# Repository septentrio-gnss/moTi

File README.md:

# moTi
| Role        | Contact                                                                 |
|-------------|-------------------------------------------------------------------------|
| Author      | [laekaz](https://github.com/laekaz)                 |
| Maintainer  | [Septentrio GNSS GitHub User](githubuser@septentrio.com)                |
| License     | [OCP CLA](https://www.opencompute.org/documents/ocp-cla)                |
| Project     | [Stargate](https://stargate-receiver.com/)    |

This project is co-funded by the European Union Agency for the Space Programme under the Fundamental Elements Grant EUSPA/GRANT/02/2024

## Table of Contents
* [Introduction](#introduction)
* [What is a moTi?](#what-is-the-moTi)
  * [Can I buy it?](#can-i-buy-it)
* [What is a Time Card?](#what-is-a-time-card)
* [What is a Mosaic-G5 T?](#what-is-a-mosaic-g5-t)
* [Who is Septentrio?](#who-is-septentrio)
  * [Why open-source?](#why-open-source)
* [Disclaimer](#disclaimer)
* [Deliverables](#deliverables)
  * [M.2 Form Factor](#m2-form-factor)
* [User Documentation](#user-documentation)
  * [System Setup](#system-setup)
    * [Boot Linux](#boot-linux)
    * [Check the GNSS Status (Satellite Time)](#check-the-gnss-status-satellite-time)
    * [Output the PPS and Clock](#output-the-pps-and-clock)
    * [Use the PHC from Linux](#use-the-phc-from-linux)
    * [When the Card is Installed and Running](#when-the-card-is-installed-and-running)
    * [If Something Goes Wrong](#if-something-goes-wrong)
* [Design Documentation](#design-documentation)
  * [Ordering Mosaic](#ordering-mosaic)
  * [Board Connections and Indicators](#board-connections-and-indicators)
    * [Pinout for M.2 Key B Connector](#pinout-for-m2-key-b-connector)
    * [USB 2.0](#usb-20)
    * [UART](#uart)
    * [PPS Out](#pps-out)
    * [Event 1 (PPS IN)](#event-1-pps-in)
    * [LED D1](#led-d1)
    * [Antenna Connector](#antenna-connector)
## Introduction 
## What is a moTi?

moTi is a timing module that provides accurate and reliable synchronisation signals for time-sensitive systems. It is based on a standardised M.2 form factor that can be easily integrated into compatible carrier boards such as the Open Compute Project (OCP) [Time Card](#what-is-a-Time-Card?).
This board receives precise timing information from Septentrio’s mosaic-G5 T GNSS (Global Navigation Satellite System) module. It then generates synchronisation outputs such as Pulse Per Second (PPS) and Time of Day (ToD) data. These signals are then used to synchronise services, in network interface cards (NICs), and other hardware in data centres and communication systems.

## What is a Time Card?

A Time Card is a PCIe card that is designed to plug into a server and provides precision time outputs such as PPS (Pulse Per Second) and ToD (Time of Day). It provides this precise timing to the server’s clock and network hardware, enabling high-accuracy synchronisation using protocols like the NTP or PTP. moTi connects to the Time Card as a timing source, supplying the card with GNSS time signals in standardised form factor.

Originally, it was developed by Meta and released through the Open Compute Project

More information about the Time Card on this [link](https://fr.scribd.com/document/803083407/M-2-Sync-Module-OCP-Base-Specification-1-1-1) or [Github](https://github.com/Time-Appliances-Project/Time-Card?tab=readme-ov-file) 

## What is a mosaic-G5 T?
[Septentrio mosaic-G5 T](https://www.septentrio.com/en/products/gnss-receivers/gnss-receiver-modules/mosaic-g5-t) is a compact, low-power GNSS timing receiver module with multi-band, multi-frequency capability. Designed for critical infrastructure and other applications where resilient and precise timing is essential, it ensures maximum security and uptime. It tracks all Global Navigation Satellite System (GNSS) constellations and supports both current and future signals. 

## Who is Septentrio?

Septentrio is a leading company that designs, manufactures and sells high precision and multi-frequency GPS/GNSS receivers for demanding applications. Septentrio products are used in different industries including automotive, marine, construction, rail, machine control, logistics, precision agriculture, geographic information systems (GIS), Unmanned Aerial Vehicles (UAVs), surveying, mapping and scientific development. Septentrio’s receivers constantly deliver accurate and precise GNSS positioning scalable to centimetre-level and designed to perform perfectly in challenging environments. 

Septentrio's technology offers high accuracy and reliability thanks to GNSS + algorithms as well as [Advanced interference Monitoring and Mitigation (AIM+)](https://www.septentrio.com/en/learn-more/advanced-positioning-technology/aim-anti-jamming-protection) This protects your application against jamming (RF interference) and spoofing (malicious attacks).

For more information about Septentrio products go to [**https://www.septentrio.com/**](https://web.septentrio.com/GH-SSN-home).

### Why open-source?
This board is open source to encourage collaboration, customization, and innovation. By making the design files publicly available, developers and engineers can study, modify, and adapt the hardware to fit their specific applications, reducing development time and cost. It also promotes transparency and avoids vendor lock-in, allowing users to fully understand and control the design.

## Disclaimer
This project is offered as-is. The main interfaces have been tested, but the design has not been fully checked or approved by the author or Septentrio. You are responsible for how you use it in your own projects. For guidance on working with Septentrio’s GNSS mosaic modules, we suggest reaching out to Septentrio directly.

Support website: https://www.septentrio.com/en/support

### Deliverables
This open-source project contains the following files for designers, producers and integrators around Septentrio's mosaic modules.
|Files         |description   |
|--------------|--------------|
|[moTi.kicad_pro](./KiCad_Files/KiCad/moTi/moTi.kicad_pro)| KiCAD project|
|[moTi.kicad_sch](./KiCad_Files/KiCad/moTi/moTi.kicad_sch)|KiCAD schematic|
|[mosaic-G5.kicad_sch](./KiCad_Files/KiCad/moTi/mosaic-G5.kicad_sch)|KiCAD mosaic-G5 schematic sheet |
|[M2_Edge connector.kicad_sch](./KiCad_Files/KiCad/moTi/M2_Edge%20connector.kicad_sch)|KiCAD M.2 Key B schematic sheet|
|[Clockdetect.kicad_sch](./KiCad_Files/KiCad/moTi/Clockdetect.kicad_sch)|KiCAD clock schematic sheet|
|[moTi.kicad_pcb](./KiCad_Files/KiCad/moTi/moTi.kicad_pcb)|KiCAD PCB layout|
|[moTi_Schematics.pdf](moTi_Schematics.pdf)|schematic PDF|

#### M.2 form factor

The M.2 form factor provides a compact interface for expansion cards.The moTi board is M.2 Key B connector, but it can also fit into some Key M or B+M slots. B+M slots are designed with extra notches so they accept both Key B and Key M modules, allowing flexibility in installation. This means your Key B board can interconnect with a Key M-compatible slot as long as it’s a B+M slot, ensuring proper electrical connections and compatibility.

## User documentation

### System Setup

Before you physically install anything: 
* Make sure you have a free PCIe slot
* Make sure your BIOS supports Virtualization/IOMMU for Linux use
* You must connect the GNSS antenna to its SMA connector before inserting the Time Card.
##### Boot Linux 
Boot Linux with the Time Card inserted. 

If your Linux system uses the Kernel 5.15 or newer the Time Card driver is already included. So the kernel loads the driver automatically.

The devices are exposed by the driver like:

`/dev/ptpX` -> PHC device 

`/dev/ppsY` -> PPS pulse signal

`/sys/class/timecard/ocp0/`-> status and attributes

These are the time interface paths in the OS.

Command example to see the devices:
```
ls -l /sys/class/timecard/ocp0/
```

This will show many devices including GNSS, PPS, PHC clock and atomic clock serial
##### Check the GNSS status (satellite time)
Once Linux has detected the Time Card:

* GNSS time is usually on a serial port like `/dev/ttyS7` or similar.
* You can run `gpsd` or a tool like `cgps` to check the satellite status.

For example:

```
gpsd /dev/ttyS5
```

* To make sure GPS is sending messages, use tio

```
tio -b 115200 /dev/ttyS5
```
* Check if the FPGA time is correct by checking the NMEA

```
tio -b 115200 /dev/ttyS0
```

##### Output the PPS and Clock
available_sma_outputs contains all available outputs

To list available outputs:
```
cat available_sma_outputs
    10MHz PHC MAC GNSS1 GNSS2 IRIG DCF GEN1 GEN2 GEN3 GEN4 GND VCC
```
```
 cat /sys/class/timecard/ocp0/available_sma_outputs 
```
Output on SMA:
* FPGA PPS 
```
echo OUT: PHC >> sma1
```
* Atomic Clock PPS
```
echo OUT: MAC >> sma1
 ```
* GPS Module's PPS 
```
echo OUT: GNSS1 >> sma1
```

##### Use the PHC from Linux
The PHC (Precision Hardware Clock) device exposed by the driver can be used to sync the Linux system clock

##### When the card is installed and running
Once everything is configured:
* The Time Card provides accurate time to Linux
* You can serve time to network clients using NTP or PTP
* Your system becomes a Stratum 1 time source 

This means your server can act as a time source for the whole infrastructure.

##### If something goes wrong
* If the driver fails to load: make sure you have a newer Linux kernel
* If /dev/ptp doesn’t show: check BIOS PCIe settings
* If no GNSS: verify if antenna is connected.

These are normal steps to get the Time Card recognized by Linux.

## Design documentation
#### Ordering mosaic
For orders of the mosaic-G5 T, please contact [Septentrio](https://www.septentrio.com/en/products/gnss-receivers/gnss-receiver-modules/mosaic-g5-t)

### Block diagram

The above block diagram is showing the overview communication between the antenna, receiver and M.2 edge connector. 

### Board connections and indicators

| interface signals |I/O Type | Voltage | Signal Description |
|-------------------|---------|---------|--------------------|
| Power             | Power   |  3.3V   |3.3 V Supply pin.   |
| UART              |   I&O   |    3.3V | Universal Asynchronous Receiver Transmitter, RX & TX|
|USB                |   I/O   |  3.3V   | Universal Serial Bus interface, USB D+ and D− differential data lines|
| PPS Out 1         |   O     | 3.3V    |Pulse Per Second signal out#1.
| PPS Out 2         |   O     | 3.3V    |Pulse Per Second signal out#2.
| Event 1 (PPS IN)  |   I     |   3.3V  |Pulse Per Second reference signal input. If not used, connect to ground on Platforms.|
| CLK_IN            |   I     | 3.3V    |10MHz reference clock input. If not used, connect to ground|
| CLK_OUT           |   O     | 3.3V    |10MHz output clock.   |
| LED D1            |   O     | 3.3V    |Power Supply indicator|

#### Pinout for M.2 Key B Connector

| Pin # |Signal            |
|-------|------------------|
| 7	    |USB D+            |
| 9	    |USB D-            |
| 23	|10MHz clock input |
| 67	|nRST_IN           |
| 2, 4	|VBAT              |
| 10	|LED#1             |
| 20	|PPS2 output       |
| 22	|Ref_CLK_SEL       |
| 24	|PPS input         |
| 46	|PPS1 output       |
| 48	|10MHz clock output|
| 62	|UART COM1 Rx      |
| 64	|UART COM1 Tx      |
| 70, 72, 74|   Power 3.3V |
| GND	|GND               |

**USB 2.0** pins USB_D+ and USB_D- 
When the module is inserted into a card that supports USB pins on its edge connector, the USB interface works just like it would on any other device. It is used for data, configuration, and control. It carries data such as , Time of Day (ToD) for the GNSS, diagnostic messages and firmware update channels. The Time Card will act as the USB host.

**UART** (Universal Asynchronous Receiver Transmitter)
This is a standard serial port using TX and RX pins.

**PPS Out** timing reference signal output. This supplies high-precision timing references directly into the Time Card clocking system. 

**Event 1 (PPS IN)** This pin detects a pulse from an external device and records the exact GNSS time when the pulse happened. It is connected to the eventB pin of the mosaic-G5 T

##### LED D1

This LED indicates whether the Module is ON/OFF

##### Antenna connector

The board provides a U.FL (UMCC) 50 Ω PCB receptacle for connecting an external GNSS antenna.
This miniature RF connector is commonly used in compact embedded and wireless systems due to its small size and reliable high-frequency performance.

**Connector Details**
* Type: U.FL (UMCC) Receptacle
* Impedance: 50 Ω
* Application: External active/passive GNSS antenna connection

**Notes**
* Use a compatible U.FL/IPX coaxial cable assembly when connecting an antenna.
* Keep RF cable lengths as short as possible to minimize signal loss.
* Ensure the antenna system is properly matched to 50 Ω impedance for optimal RF performance.

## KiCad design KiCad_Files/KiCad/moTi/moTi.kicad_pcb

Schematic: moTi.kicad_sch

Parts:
PCB1: PCB_label

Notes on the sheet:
Project: moTi Varient: mosaic-G5 T
CHANGE LOG
mosaic-G5 T
Ultra-compact high-precision GNSS time synchronization receiver
Table of content
M.2 Key B with Mosaic G5 GNSS Module
Schematics arranged by Laetitia.K

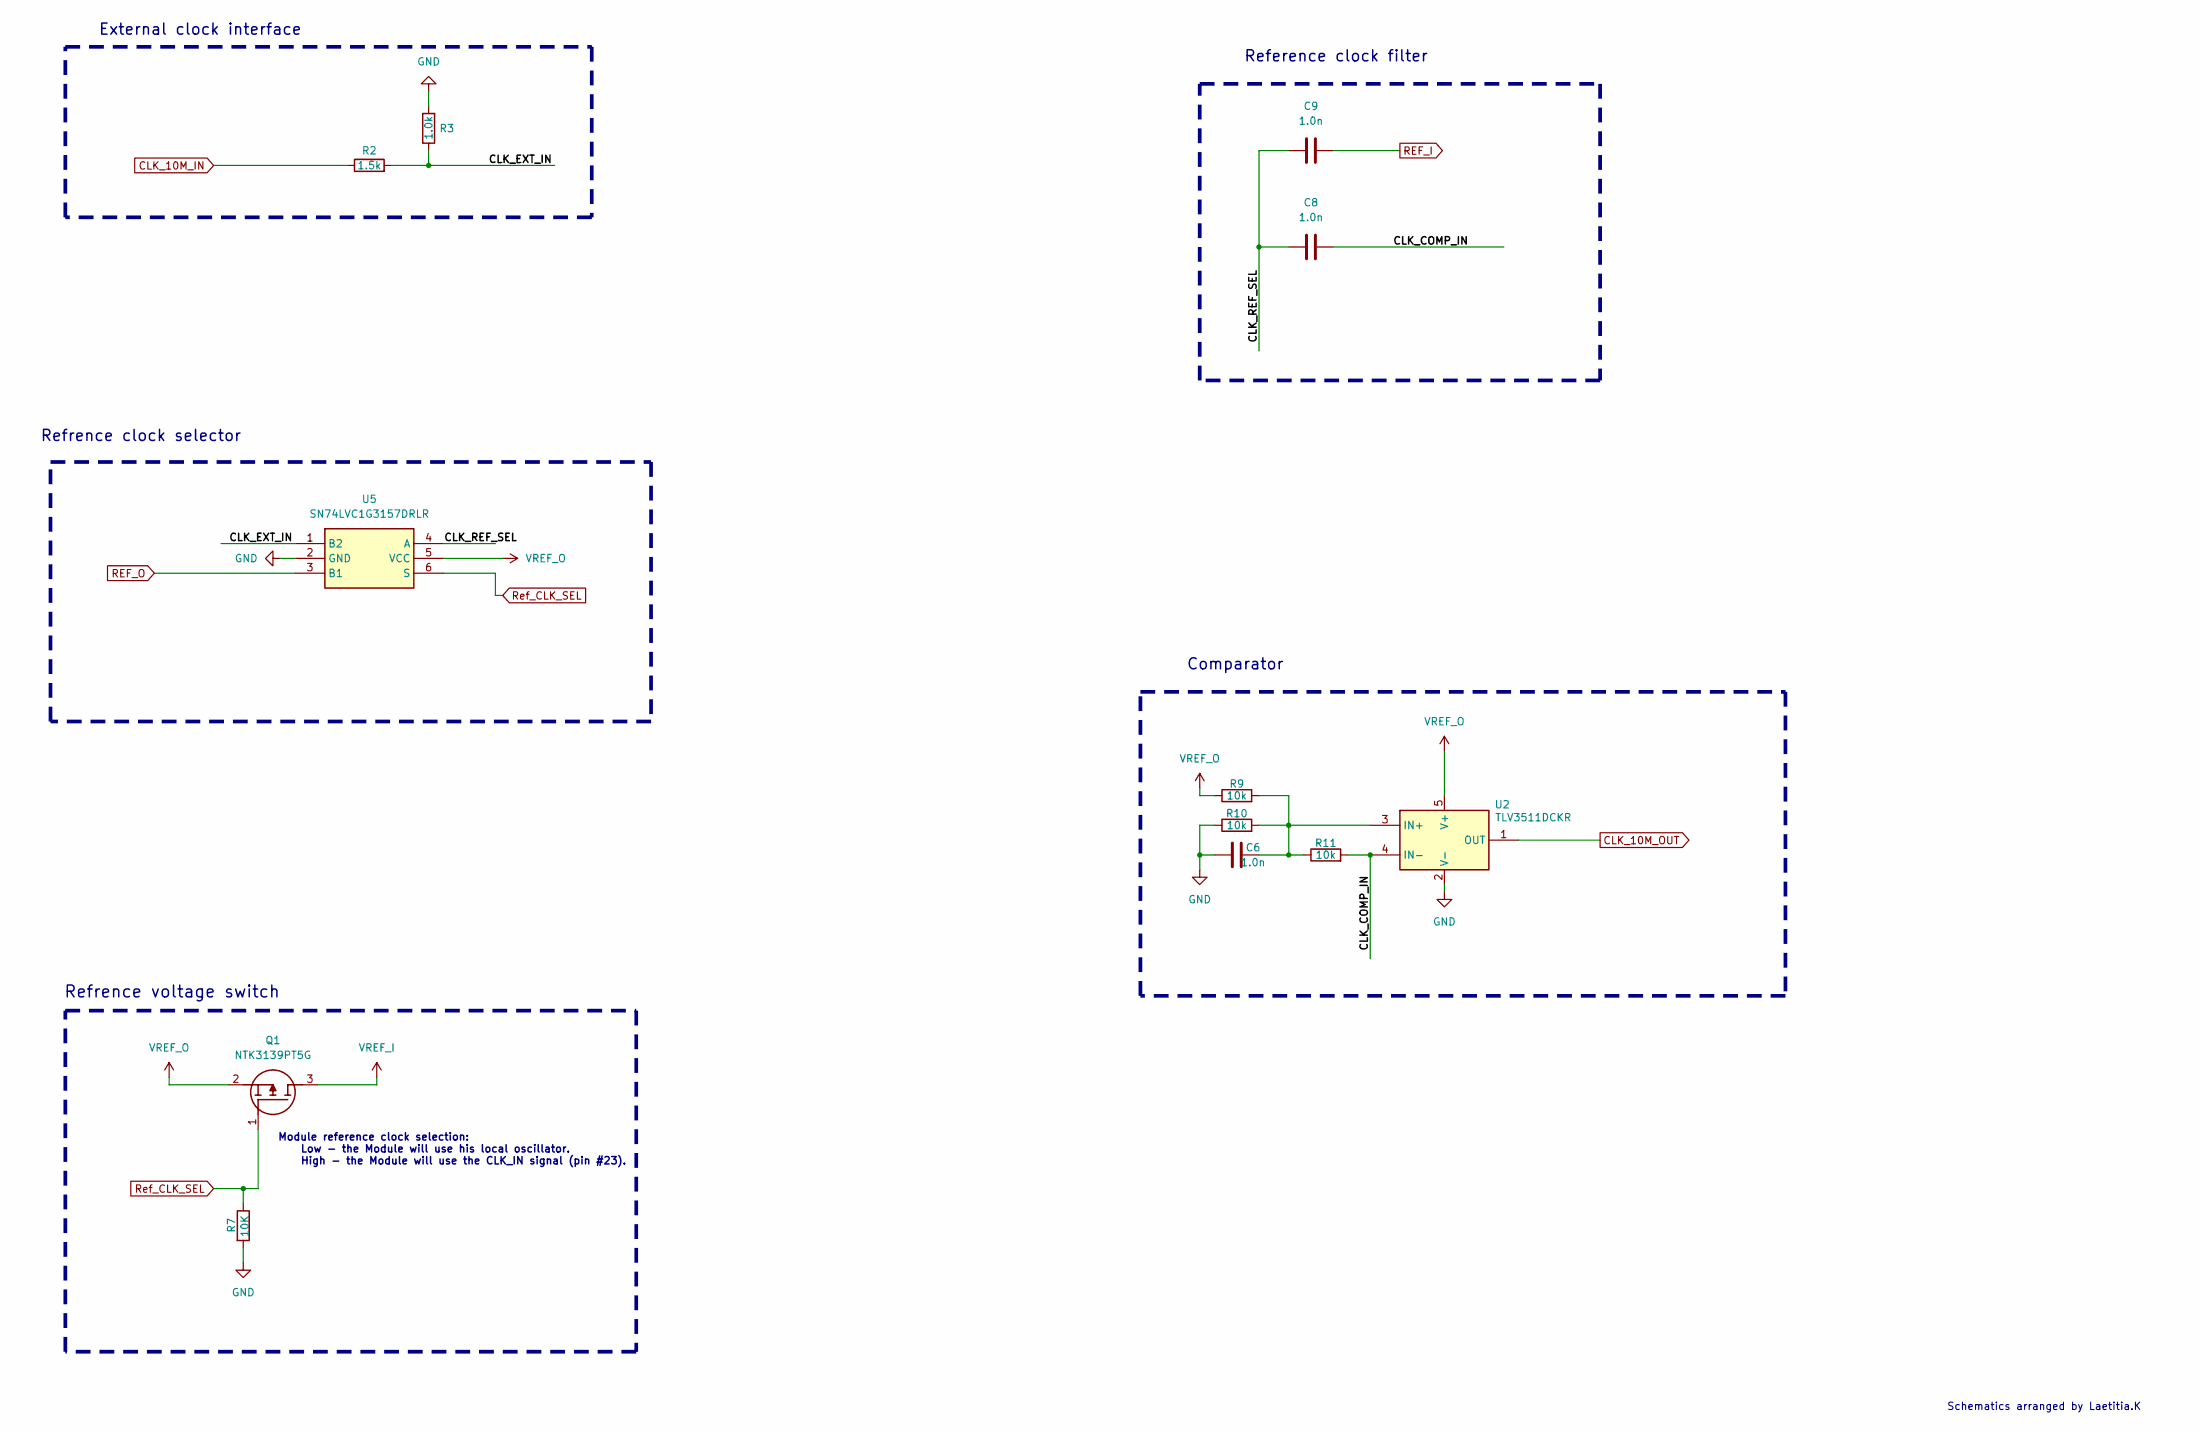
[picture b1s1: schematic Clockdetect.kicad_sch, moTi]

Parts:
C6, C8, C9: 1.0n; C_0402_1005Metric; Manufacturer_Part_Number CC0402KRX7R9BB102
Q1: NTK3139PT5G; SOTFL40P120X55-3N; Manufacturer_Part_Number NTK3139PT5G; Mouser Part Number 863-NTK3139PT5G
R2: 1.5k; R_0402_1005Metric; Manufacturer_Part_Number CRCW04022K20FKED
R3: 1.0k; R_0402_1005Metric; Manufacturer_Part_Number CRCW04021K00FKEDC
R7: 10K
R9, R10, R11: 10k; R_0402_1005Metric; Manufacturer_Part_Number CRCW040210K0FKED
U2: TLV3511DCKR; SOT65P210X110-5N; Manufacturer_Part_Number TLV3511DCKR
U5: SN74LVC1G3157DRLR; SOTFL50P160X60-6N; Mouser Part Number 595-SN74LVC1G3157DRL

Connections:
CLK_10M_IN: R2.1; also elsewhere on the board
CLK_10M_OUT: U2.1 (OUT); also elsewhere on the board
unnamed: C6.2, R9.2, R10.2, R11.1, U2.3 (IN+)
unnamed: C8.2, R11.2, U2.4 (IN-)
unnamed: C8.1, C9.1, U5.4 (A)
unnamed: R2.2, R3.1, U5.1 (B2)
REF_I: C9.2; also elsewhere on the board
REF_O: U5.3 (B1); also elsewhere on the board
VREF_I: Q1.3 (D); also elsewhere on the board
VREF_O: Q1.2 (S), R9.1, U2.5 (V+), U5.5 (VCC); also elsewhere on the board

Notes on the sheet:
Comparator
External clock interface
Reference clock filter
Refrence clock selector
Refrence voltage switch
Module reference clock selection: Low - the Module will use his local oscillator. High - the Module will use the CLK_IN signal (pin #23).
Schematics arranged by Laetitia.K

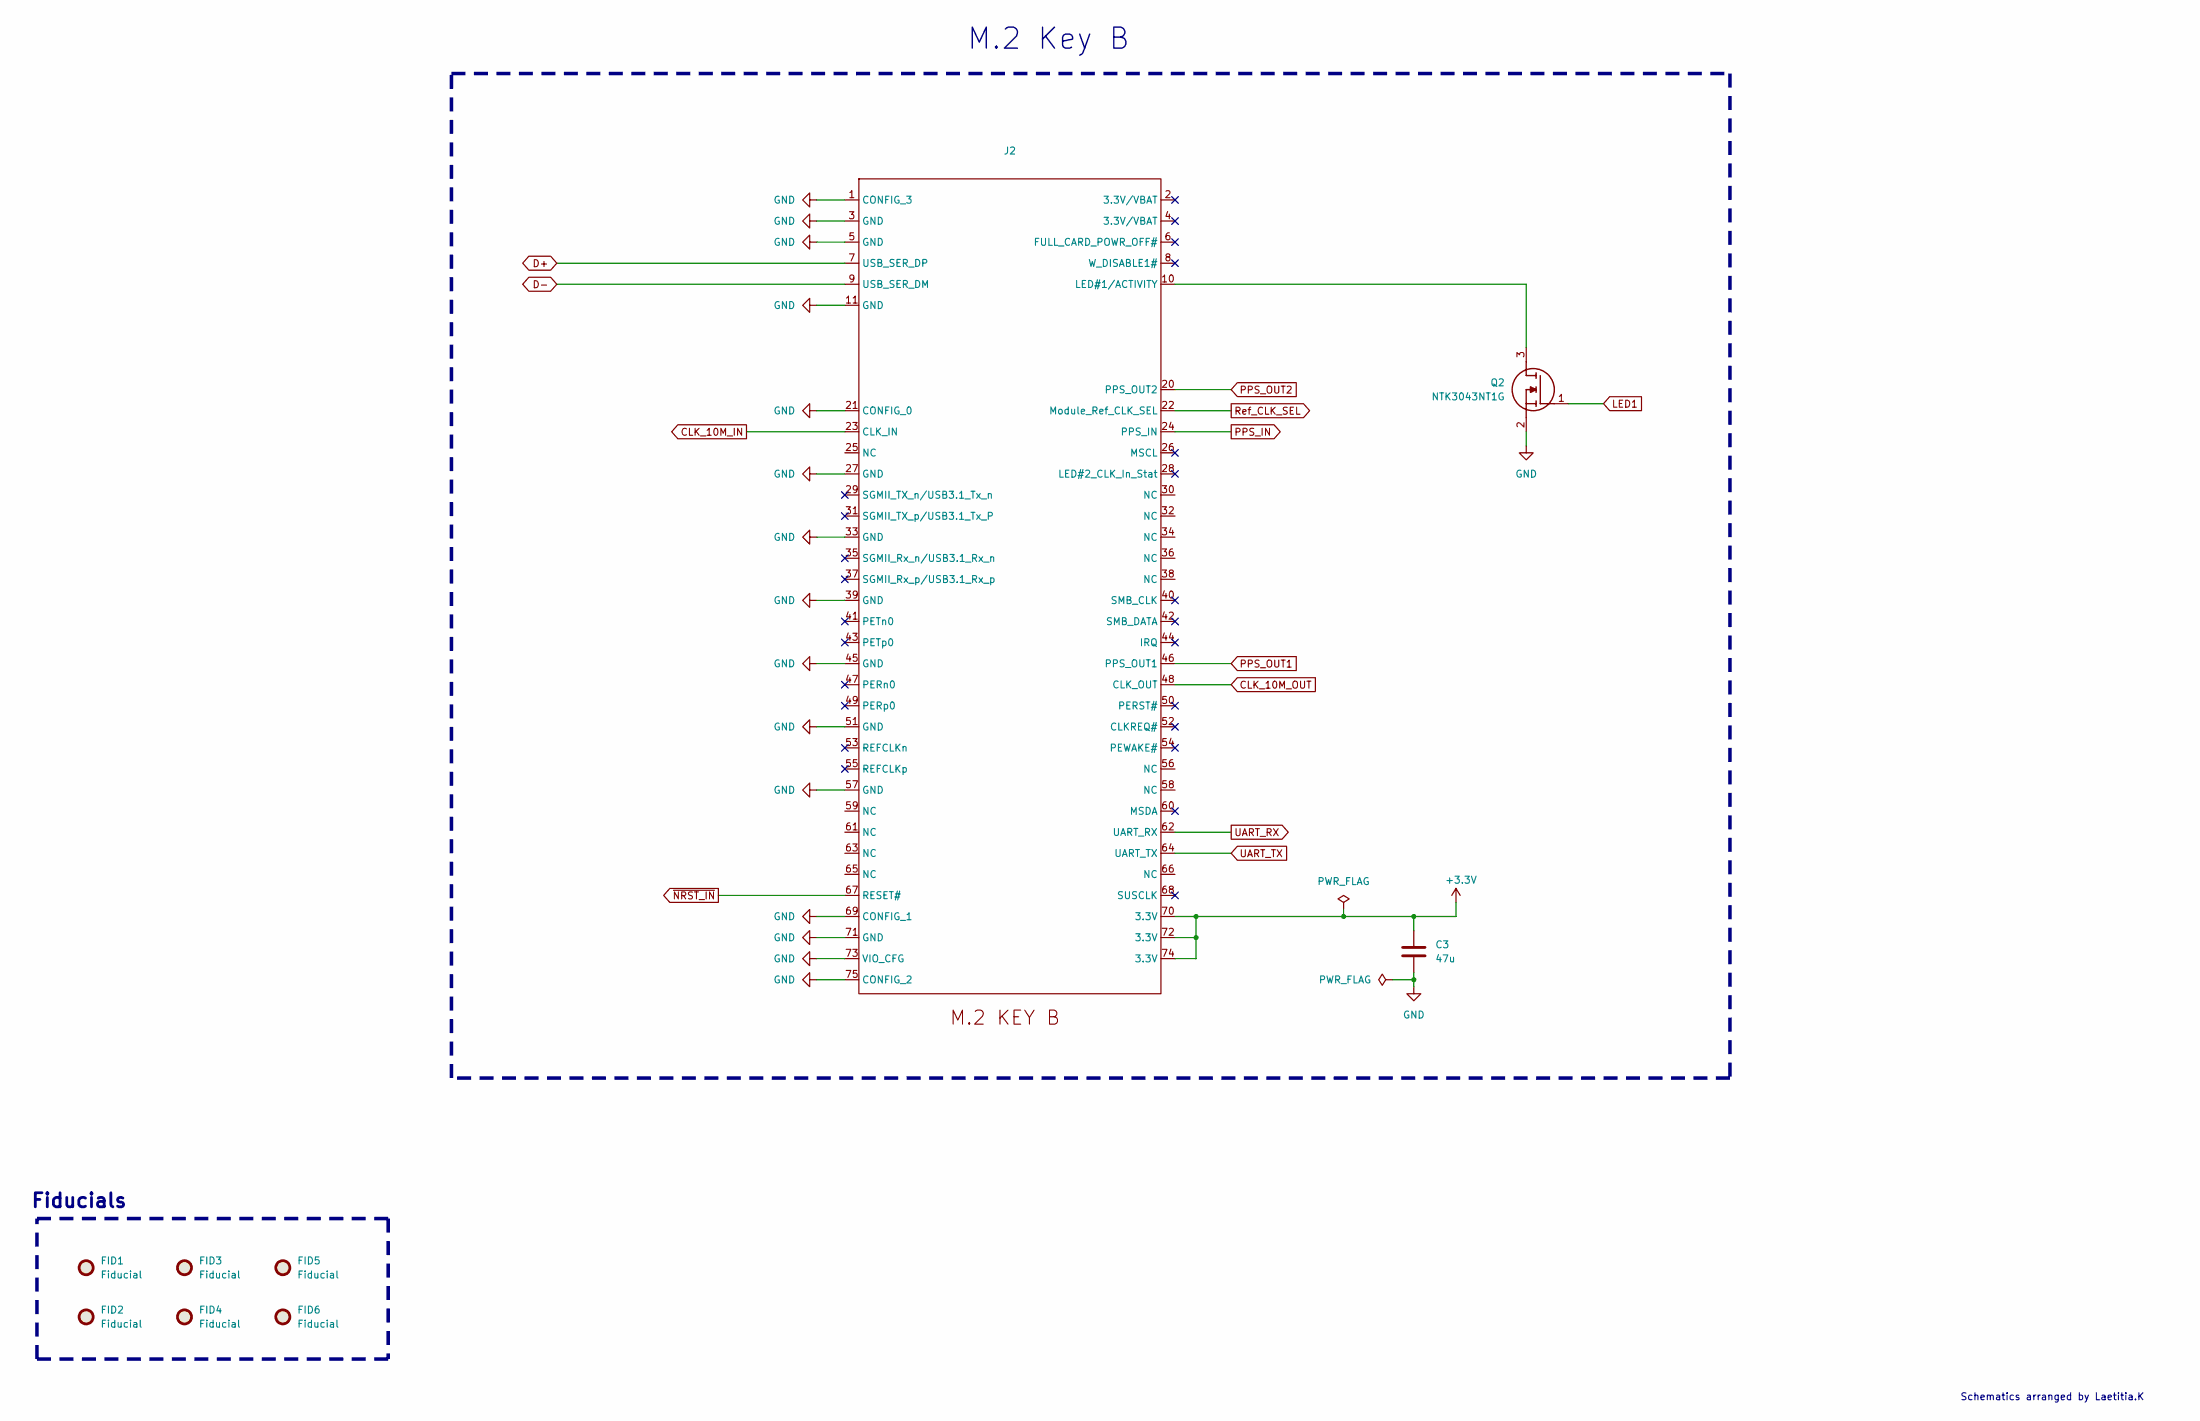
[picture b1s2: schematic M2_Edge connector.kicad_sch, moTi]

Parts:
C3: 47u; C_0805_2012Metric; Manufacturer_Part_Number GRM21BR61A476ME15L
FID1, FID2, FID3, FID4, FID5, FID6: Fiducial; Fiducial_0.5mm_Mask1mm
J2: NGFF_B
Q2: NTK3043NT1G; MMBT2907AM3T5G; Mouser Part Number 863-NTK3043NT1G

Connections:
+3.3V: C3.1, J2.70 (3.3V), J2.72 (3.3V), J2.74 (3.3V); also elsewhere on the board
CLK_10M_IN: J2.23 (CLK_IN); also elsewhere on the board
CLK_10M_OUT: J2.48 (CLK_OUT); also elsewhere on the board
D+: J2.7 (USB_SER_DP); also elsewhere on the board
D-: J2.9 (USB_SER_DM); also elsewhere on the board
LED1: Q2.1 (G); also elsewhere on the board
unnamed: J2.10 (LED#1/ACTIVITY), Q2.3 (D)
PPS_IN: J2.24 (PPS_IN); also elsewhere on the board
PPS_OUT1: J2.46 (PPS_OUT1); also elsewhere on the board
PPS_OUT2: J2.20 (PPS_OUT2); also elsewhere on the board
UART_RX: J2.62 (UART_RX); also elsewhere on the board
UART_TX: J2.64 (UART_TX); also elsewhere on the board
~NRST_IN: J2.67 (RESET#); also elsewhere on the board

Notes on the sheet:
M.2 Key B
Fiducials
Schematics arranged by Laetitia.K

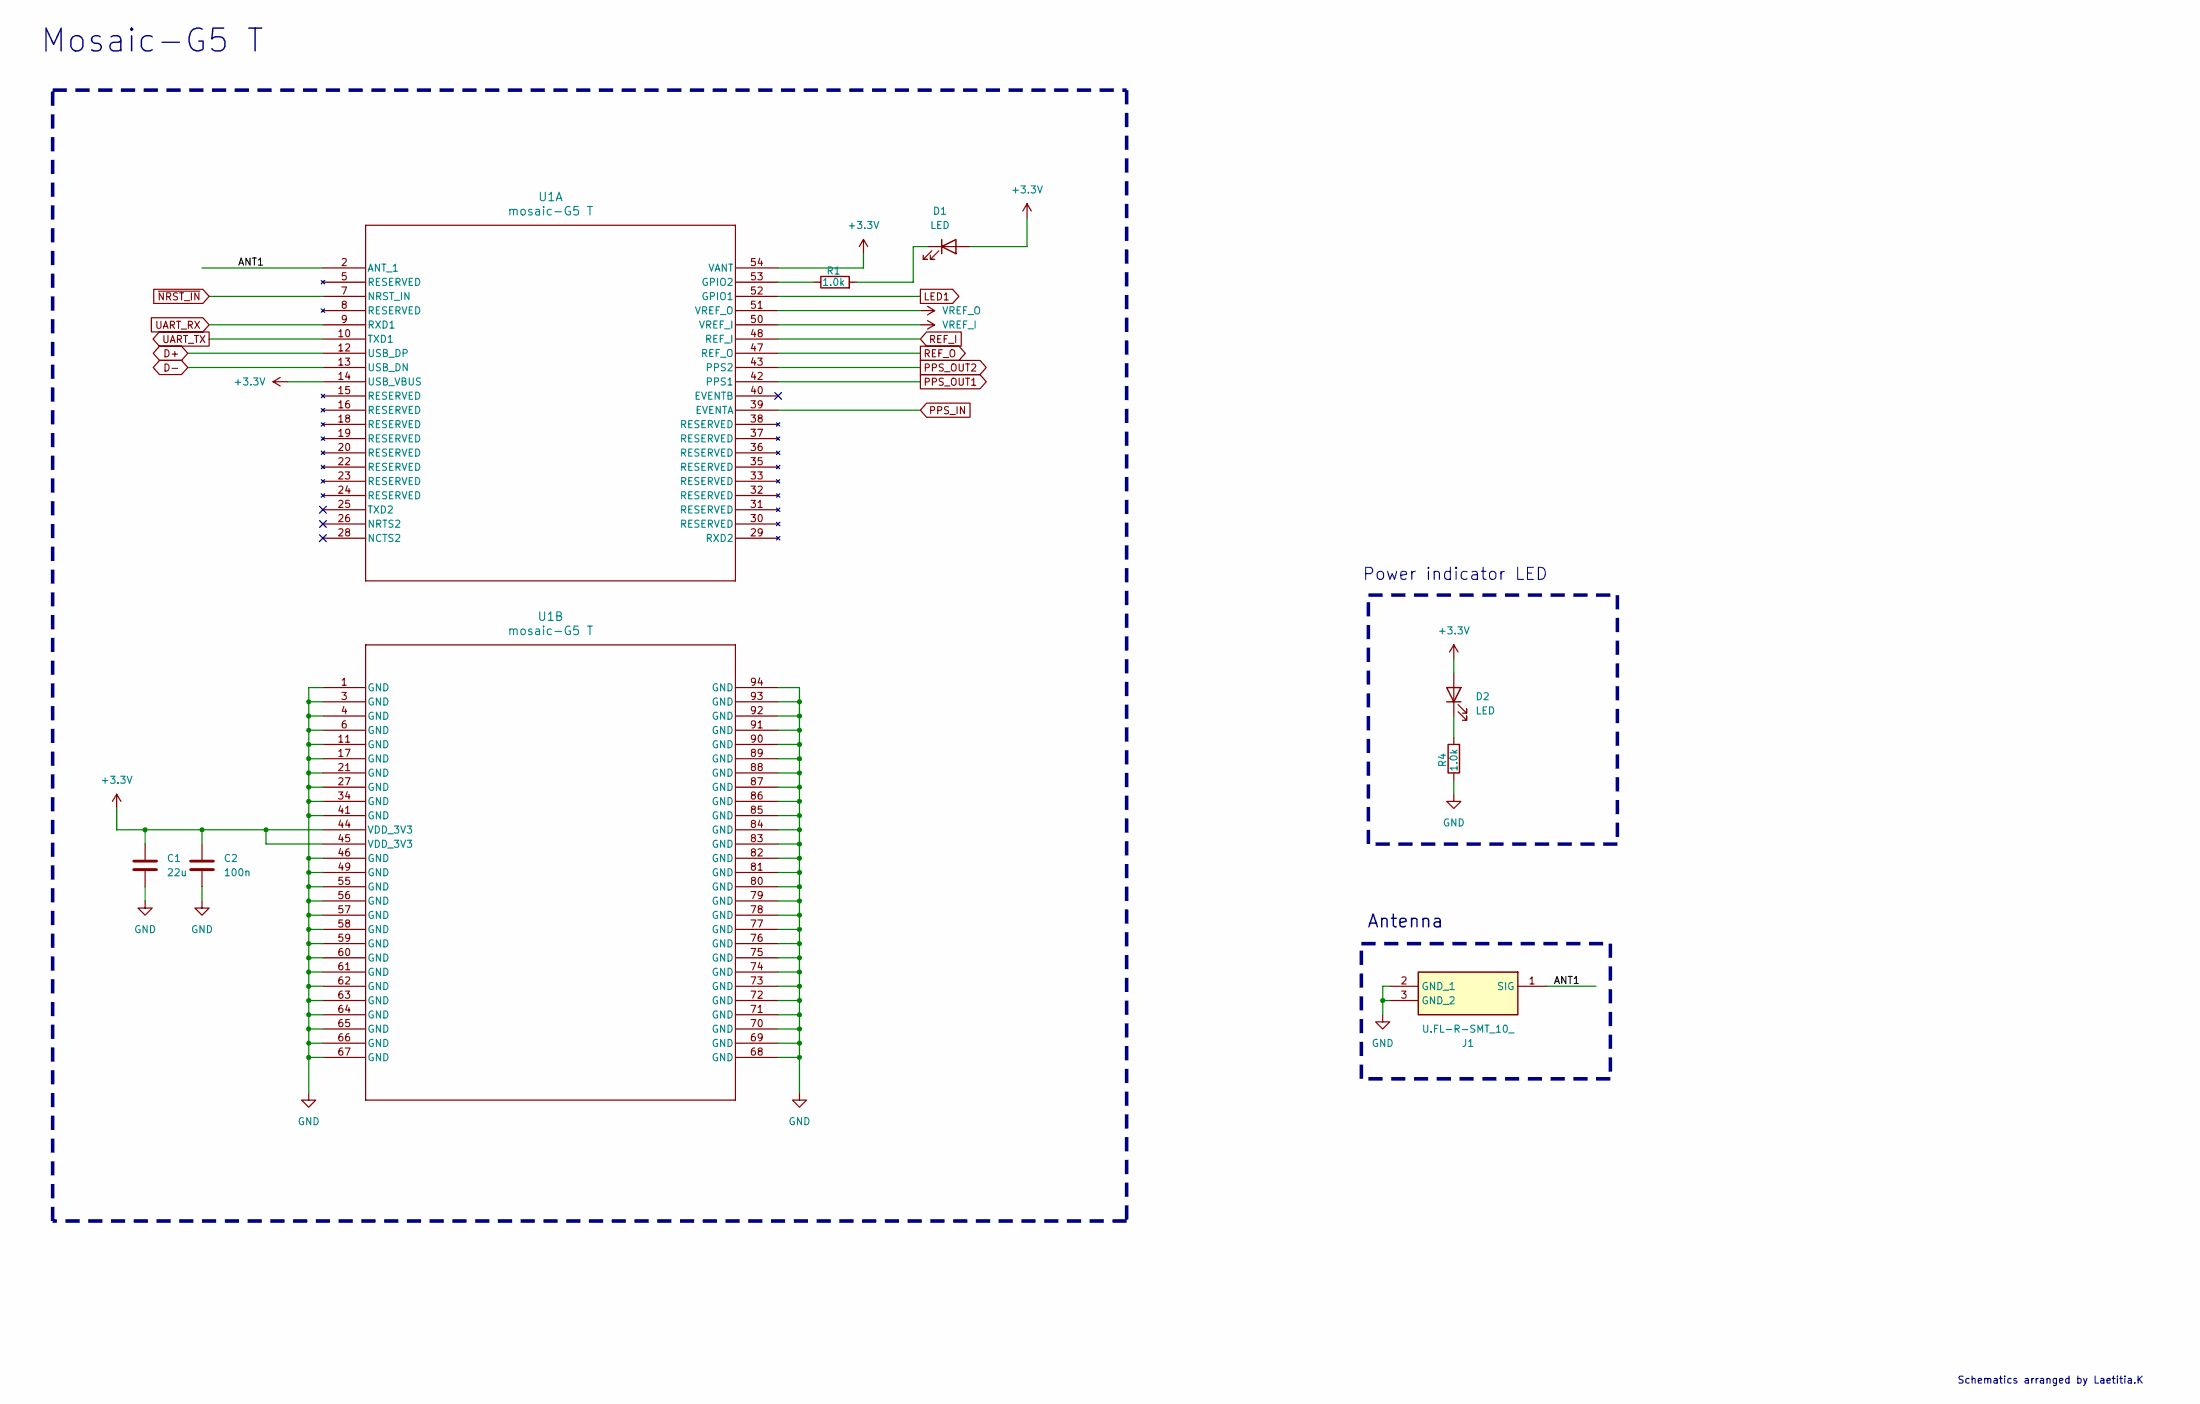
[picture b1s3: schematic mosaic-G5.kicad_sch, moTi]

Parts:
C1: 22u; C_0805_2012Metric; Manufacturer_Part_Number GRM21BC81C226ME44L
C2: 100n; C_0402_1005Metric; Manufacturer_Part_Number CC0402KRX7R7BB104
D1, D2: LED; LED_0603_1608Metric; Manufacturer_Part_Number LTST-C191KGKT
J1: U.FL-R-SMT_10_; UFLRSMT10; Mouser Part Number 798-U.FL-R-SMT10
R1, R4: 1.0k; R_0402_1005Metric; Manufacturer_Part_Number CRCW04021K00FKEDC
U1: mosaic-G5 T; LGA54_MOSAIC-MINI_SEP

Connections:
+3.3V: C1.1, C2.1, D1.2 (A), D2.2 (A), U1.14 (USB_VBUS), U1.44 (VDD_3V3), U1.45 (VDD_3V3), U1.54 (VANT); also elsewhere on the board
/mosaic-G5/ANT1: J1.1 (SIG), U1.2 (ANT_1)
D+: U1.12 (USB_DP); also elsewhere on the board
D-: U1.13 (USB_DN); also elsewhere on the board
LED1: U1.52 (GPIO1); also elsewhere on the board
unnamed: D1.1 (K), R1.2
unnamed: D2.1 (K), R4.2
unnamed: R1.1, U1.53 (GPIO2)
PPS_IN: U1.39 (EVENTA); also elsewhere on the board
PPS_OUT1: U1.42 (PPS1); also elsewhere on the board
PPS_OUT2: U1.43 (PPS2); also elsewhere on the board
REF_I: U1.48 (REF_I); also elsewhere on the board
REF_O: U1.47 (REF_O); also elsewhere on the board
UART_RX: U1.9 (RXD1); also elsewhere on the board
UART_TX: U1.10 (TXD1); also elsewhere on the board
VREF_I: U1.50 (VREF_I); also elsewhere on the board
VREF_O: U1.51 (VREF_O); also elsewhere on the board
~NRST_IN: U1.7 (NRST_IN); also elsewhere on the board

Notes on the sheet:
Mosaic-G5 T
Antenna
Power indicator LED
Schematics arranged by Laetitia.K

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
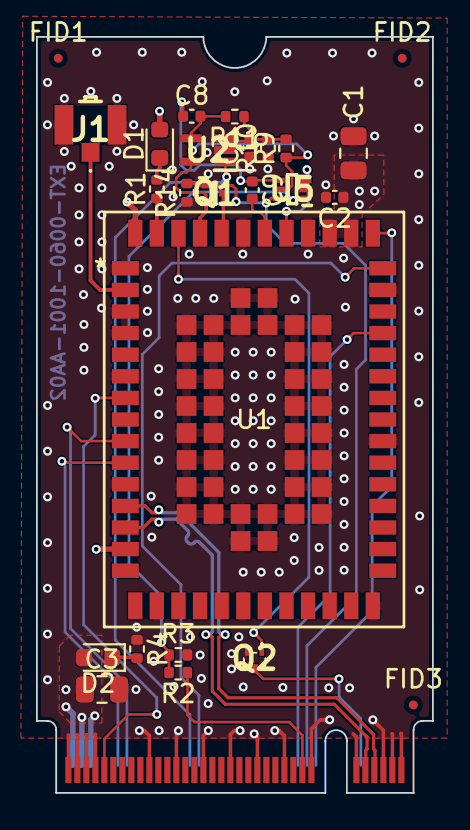
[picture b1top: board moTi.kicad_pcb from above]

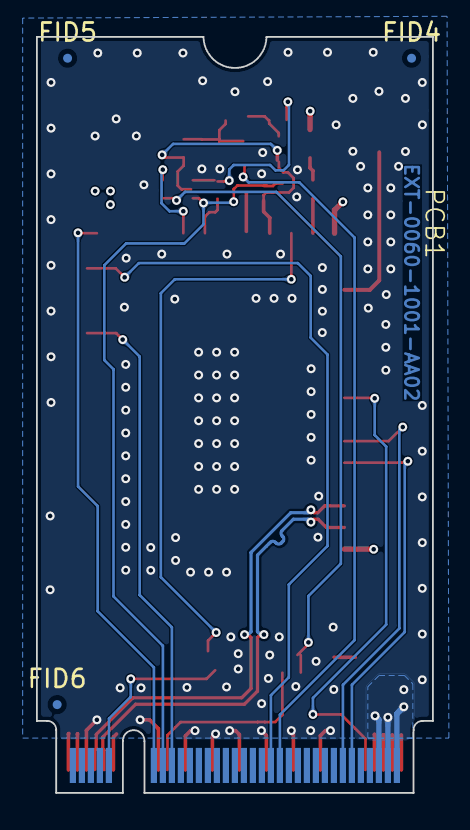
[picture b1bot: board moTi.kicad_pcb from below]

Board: 4 copper layers, 22.0 x 42.0 mm, 30 parts (4 on the bottom side), 27 nets.

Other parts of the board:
R14: 10k; R_0402_1005Metric

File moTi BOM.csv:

Reference,Value,Description,Qty,Manufacturer_Name,Manufacturer_Part_Number
C1,22u,Unpolarized capacitor,1,Murata Electronics,GRM21BC81C226ME44L
C2,100n,Unpolarized capacitor,1,YAGEO,CC0402KRX7R7BB104
C3,47u,CAP CER 47UF 10V X5R 0805,1,Murata Electronics,GRM21BR61A476ME15L
C8,1.0n,Unpolarized capacitor,1,YAGEO,CC0402KRX7R9BB102
C9,1.0n,Unpolarized capacitor,1,YAGEO,CC0402KRX7R9BB102
D1,LED,Light emitting diode,1,LITEON,LTST-C191KGKT
D2,LED,Light emitting diode,1,LITEON,LTST-C191KGKT
J1,U.FL-R-SMT_10_,"U.FL (UMCC) Connector Receptacle, Male Pin 50 Ohms Surface Mount Solder",1,Hirose,U.FL-R-SMT(10)
Q1,NTK3139PT5G,"P-channel Switch with Low RDS(on); 44% Smaller Footprint and 38% Thinner than SC-89; Low Threshold Levels, 1.5 V RDS(on) Rating; RoHS Compliant; Operated at Low Logic Level Gate Drive",1,onsemi,NTK3139PT5G
Q2,NTK3043NT1G,"Enables High Density PCB Manufacturing; 44% Smaller Footprint than SC-89 and 38% Thinner than SC-89; Low Voltage Drive Makes this Device Ideal for Portable Equipment; Low Threshold Levels, VGS(TH) < 1.3 V; Low Profile (< 0.5 mm) Allows It to Fit Easily in Extremely Thin Environments such as Protable Electronics.; Operated at Standard Logic Level Gate Drive, Facilitating Future Migration to Lower Levels Using the Same Basic Topolgy.",1,onsemi,NTK3043NT1G
R1,1.0k,Resistor,1,Vishay,CRCW04021K00FKEDC
R10,10k,Resistor,1,Vishay,CRCW040210K0FKED
R11,10k,Resistor,1,Vishay,CRCW040210K0FKED
R2,1.5k,Resistor,1,Vishay,CRCW04022K20FKED
R3,1.0k,Resistor,1,Vishay,CRCW04021K00FKEDC
R4,1.0k,Resistor,1,Vishay,CRCW04021K00FKEDC
R7,10k,Resistor,1,Vishay,CRCW040210K0FKED
R8,4k7,Resistor,1,Vishay,CRCW04024K70FKED
R9,10k,Resistor,1,Vishay,CRCW040210K0FKED
U1,mosaic-G5 T,GNSS timing receiver,1,Septentrio,410504
U2,TLV3511DCKR,"Comparator General Purpose Push-Pull, Rail-to-Rail SC-70-5 ,2.7V ~ 5.5V ,85mA @ 5V ,2.3mV ,-40C ~ 125C ,SC-70-5",1,Texas Instruments,TLV3511DCKR
U5,SN74LVC1G3157DRLR,"Single-Pole, Double-Throw Analog Switch",1,Texas Instruments,SN74LVC1G3157DRLR

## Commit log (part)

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2026-03-04 KiCad folder
2026-03-10 feedback update
2026-03-10 KiCad update
2026-03-11 picture edit
2026-03-11 connection update
2026-03-15 HW files update
2026-03-20 Septentrio logo
2026-03-20 schematic pdf
2026-03-22 update m.2 connector pic
2026-03-25 connectors
2026-04-20 HW file update
2026-05-26 I2C change
2026-05-26 BOM update
2026-05-26 schematic pdf update
2026-05-27 kicad file clean up
2026-05-27 kicad clean up
2026-06-01 general clean up
2026-06-02 CAD file
    Plus documentation update
2026-06-02 readme update
2026-06-04 BOM
    xml files from library and BOM
2026-06-04 Update .gitignore to remove BOM file exclusions
    Remove exported BOM file patterns from .gitignore
